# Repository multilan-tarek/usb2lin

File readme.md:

## USB2LIN

This is a 4-channel interface for LIN buses.\
It is using 4 NXP TJA1021 and a MaxLinear XR21V1414IM USB to UART bridge. 

Tested with BMW I/K-Bus, but it should work with any LIN bus.

---

### Gerber Files 
The gerber file is ready for ordering at JLCPCB.

### Parts
The schematic contains LCSC part numbers which can be exported to a BOM.

### Udev rules
This repository contains a udev rules file that maps the UART ports to ```/dev/lin/a@,b@,c@,d@```, matching the boards silkscreen.

---

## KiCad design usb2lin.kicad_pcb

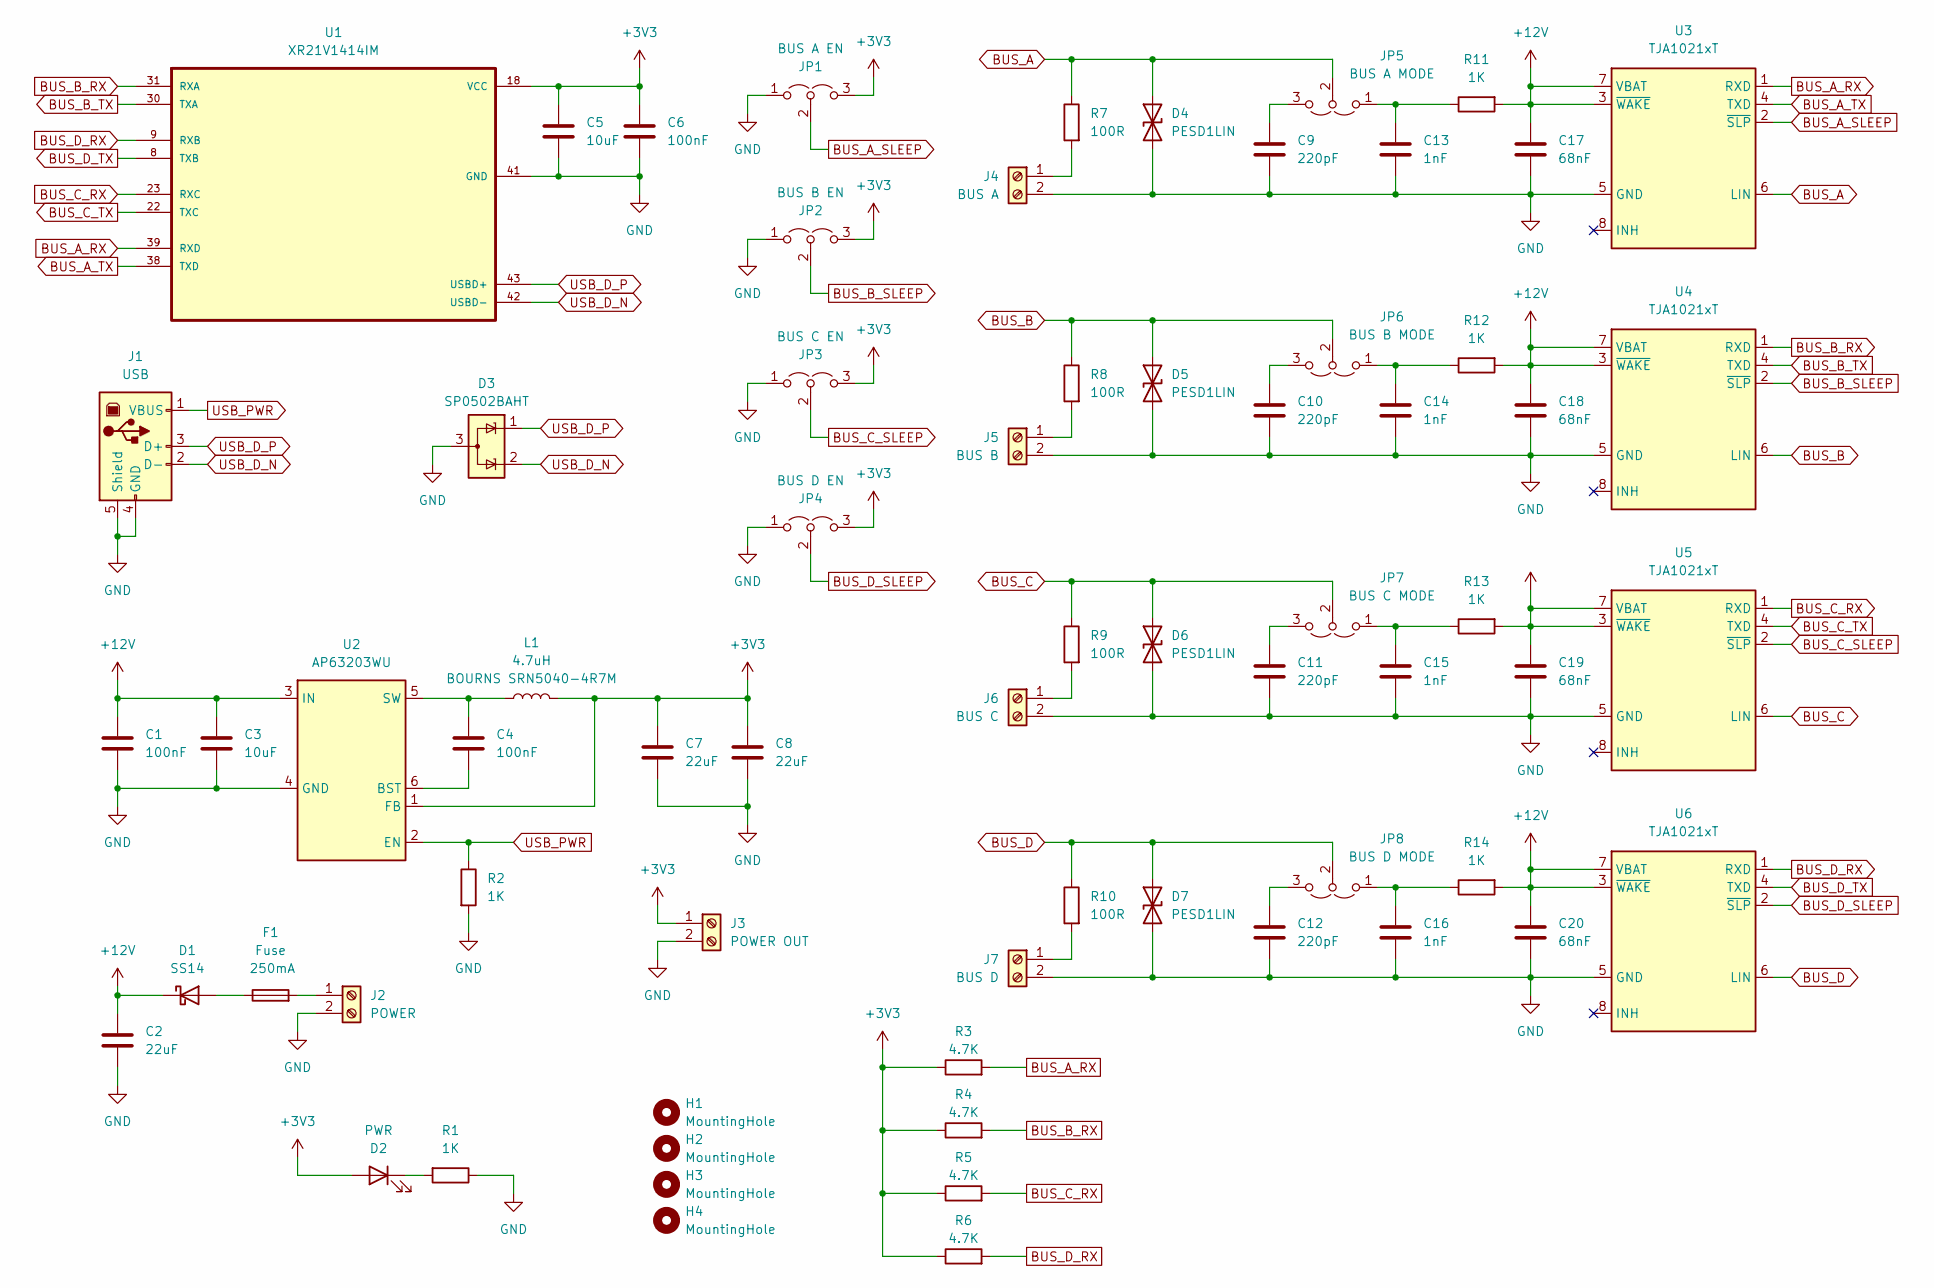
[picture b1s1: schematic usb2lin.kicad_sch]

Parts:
C1, C4, C6: 100nF; C_0805_2012Metric; LCSC C1711
C2, C7, C8: 22uF; C_0805_2012Metric; LCSC C602037
C3, C5: 10uF; C_0805_2012Metric; LCSC C15850
C9, C10, C11, C12: 220pF; C_0805_2012Metric; LCSC C472838
C13, C14, C15, C16: 1nF; C_0805_2012Metric; LCSC C46653
C17, C18, C19, C20: 68nF; C_0805_2012Metric; LCSC C472830
D1: SS14; D_SMA; LCSC C83852
D2: PWR; LED_0805_2012Metric; LCSC C94868
D3: SP0502BAHT; SOT-23; LCSC C207261
D4, D5, D6, D7: PESD1LIN; D_SOD-323; LCSC C58901
F1: Fuse; Fuse_1206_3216Metric_Pad1.42x1.75mm_HandSolder; LCSC C83557
H1, H2, H3, H4: MountingHole; MountingHole_3.2mm_M3
J1: USB; USB_B_TE_5787834_Vertical; LCSC C592900
J2: POWER; TerminalBlock_TE_282834-2_1x02_P2.54mm_Horizontal; LCSC C592983
J3: POWER OUT; TerminalBlock_TE_282834-2_1x02_P2.54mm_Horizontal; LCSC C592983
J4: BUS A; TerminalBlock_TE_282834-2_1x02_P2.54mm_Horizontal; LCSC C592983
J5: BUS B; TerminalBlock_TE_282834-2_1x02_P2.54mm_Horizontal; LCSC C592983
J6: BUS C; TerminalBlock_TE_282834-2_1x02_P2.54mm_Horizontal; LCSC C592983
J7: BUS D; TerminalBlock_TE_282834-2_1x02_P2.54mm_Horizontal; LCSC C592983
JP1: BUS A EN; PinHeader_1x03_P2.54mm_Vertical; LCSC C2937625
JP2: BUS B EN; PinHeader_1x03_P2.54mm_Vertical; LCSC C2937625
JP3: BUS C EN; PinHeader_1x03_P2.54mm_Vertical; LCSC C2937625
JP4: BUS D EN; PinHeader_1x03_P2.54mm_Vertical; LCSC C2937625
JP5: BUS A MODE; PinHeader_1x03_P2.54mm_Vertical; LCSC C2937625
JP6: BUS B MODE; PinHeader_1x03_P2.54mm_Vertical; LCSC C2937625
JP7: BUS C MODE; PinHeader_1x03_P2.54mm_Vertical; LCSC C2937625
JP8: BUS D MODE; PinHeader_1x03_P2.54mm_Vertical; LCSC C2937625
L1: 4.7uH; L_APV_ANR5040; LCSC C2041710
R1, R2, R11, R12, R13, R14: 1K; R_0805_2012Metric; LCSC C441981
R3, R4, R5, R6: 4.7K; R_0805_2012Metric; LCSC C336873
R7, R8, R9, R10: 100R; R_0805_2012Metric; LCSC C193990
U1: XR21V1414IM; TQFP-48_7x7mm_P0.5mm; MPN XR21V1414IM-0B-EB; LCSC C141719
U2: AP63203WU; TSOT-23-6; LCSC C780769
U3, U4, U5, U6: TJA1021xT; SOIC-8_3.9x4.9mm_P1.27mm; LCSC C182937

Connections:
+3V3: C5.1, C6.1, C7.1, C8.1, D2.2 (A), J3.1, JP1.3 (B), JP2.3 (B), JP3.3 (B), JP4.3 (B), L1.2, R3.1, R4.1, R5.1, R6.1, U1.5 (VCC), U1.18 (VCC), U1.33 (VCC), U1.44 (VCC), U1.45 (VCC), U2.1 (FB)
+12V: C1.1, C2.1, C3.1, C17.1, C18.1, C19.1, C20.1, D1.1 (K), R11.2, R12.2, R13.2, R14.2, U2.3 (IN), U3.3 (~WAKE), U3.7 (VBAT), U4.3 (~WAKE), U4.7 (VBAT), U5.3 (~WAKE), U5.7 (VBAT), U6.3 (~WAKE), U6.7 (VBAT)
BUS_A: D4.1 (A1), JP5.2 (C), R7.1, U3.6 (LIN)
BUS_A_RX: R3.2, U1.39 (RXD), U3.1 (RXD)
BUS_A_SLEEP: JP1.2 (C), U3.2 (~SLP)
BUS_A_TX: U1.38 (TXD), U3.4 (TXD)
BUS_B: D5.1 (A1), JP6.2 (C), R8.1, U4.6 (LIN)
BUS_B_RX: R4.2, U1.31 (RXA), U4.1 (RXD)
BUS_B_SLEEP: JP2.2 (C), U4.2 (~SLP)
BUS_B_TX: U1.30 (TXA), U4.4 (TXD)
BUS_C: D6.1 (A1), JP7.2 (C), R9.1, U5.6 (LIN)
BUS_C_RX: R5.2, U1.23 (RXC), U5.1 (RXD)
BUS_C_SLEEP: JP3.2 (C), U5.2 (~SLP)
BUS_C_TX: U1.22 (TXC), U5.4 (TXD)
BUS_D: D7.1 (A1), JP8.2 (C), R10.1, U6.6 (LIN)
BUS_D_RX: R6.2, U1.9 (RXB), U6.1 (RXD)
BUS_D_SLEEP: JP4.2 (C), U6.2 (~SLP)
BUS_D_TX: U1.8 (TXB), U6.4 (TXD)
GND: C1.2, C2.2, C3.2, C5.2, C6.2, C7.2, C8.2, C9.2, C10.2, C11.2, C12.2, C13.2, C14.2, C15.2, C16.2, C17.2, C18.2, C19.2, C20.2, D3.3 (A), D4.2 (A2), D5.2 (A2), D6.2 (A2), D7.2 (A2), J1.4 (GND), J1.5 (Shield), J2.2, J3.2, J4.2, J5.2, J6.2, J7.2, JP1.1 (A), JP2.1 (A), JP3.1 (A), JP4.1 (A), R1.1, R2.2, U1.1 (GND), U1.4 (GND), U1.19 (GND), U1.32 (GND), U1.40 (GND), U1.41 (GND), U2.4 (GND), U3.5 (GND), U4.5 (GND), U5.5 (GND), U6.5 (GND)
unnamed: D1.2 (A), F1.1
unnamed: D2.1 (K), R1.2
unnamed: F1.2, J2.1
unnamed: J4.1, R7.2
unnamed: J5.1, R8.2
unnamed: J6.1, R9.2
unnamed: J7.1, R10.2
unnamed: C13.1, JP5.1 (A), R11.1
unnamed: C9.1, JP5.3 (B)
unnamed: C14.1, JP6.1 (A), R12.1
unnamed: C10.1, JP6.3 (B)
unnamed: C15.1, JP7.1 (A), R13.1
unnamed: C11.1, JP7.3 (B)
unnamed: C16.1, JP8.1 (A), R14.1
unnamed: C12.1, JP8.3 (B)
unnamed: C4.2, U2.6 (BST)
unnamed: C4.1, L1.1, U2.5 (SW)
USB_D_N: D3.2 (K), J1.2 (D-), U1.42 (USBD-)
USB_D_P: D3.1 (K), J1.3 (D+), U1.43 (USBD+)
USB_PWR: J1.1 (VBUS), R2.1, U2.2 (EN)

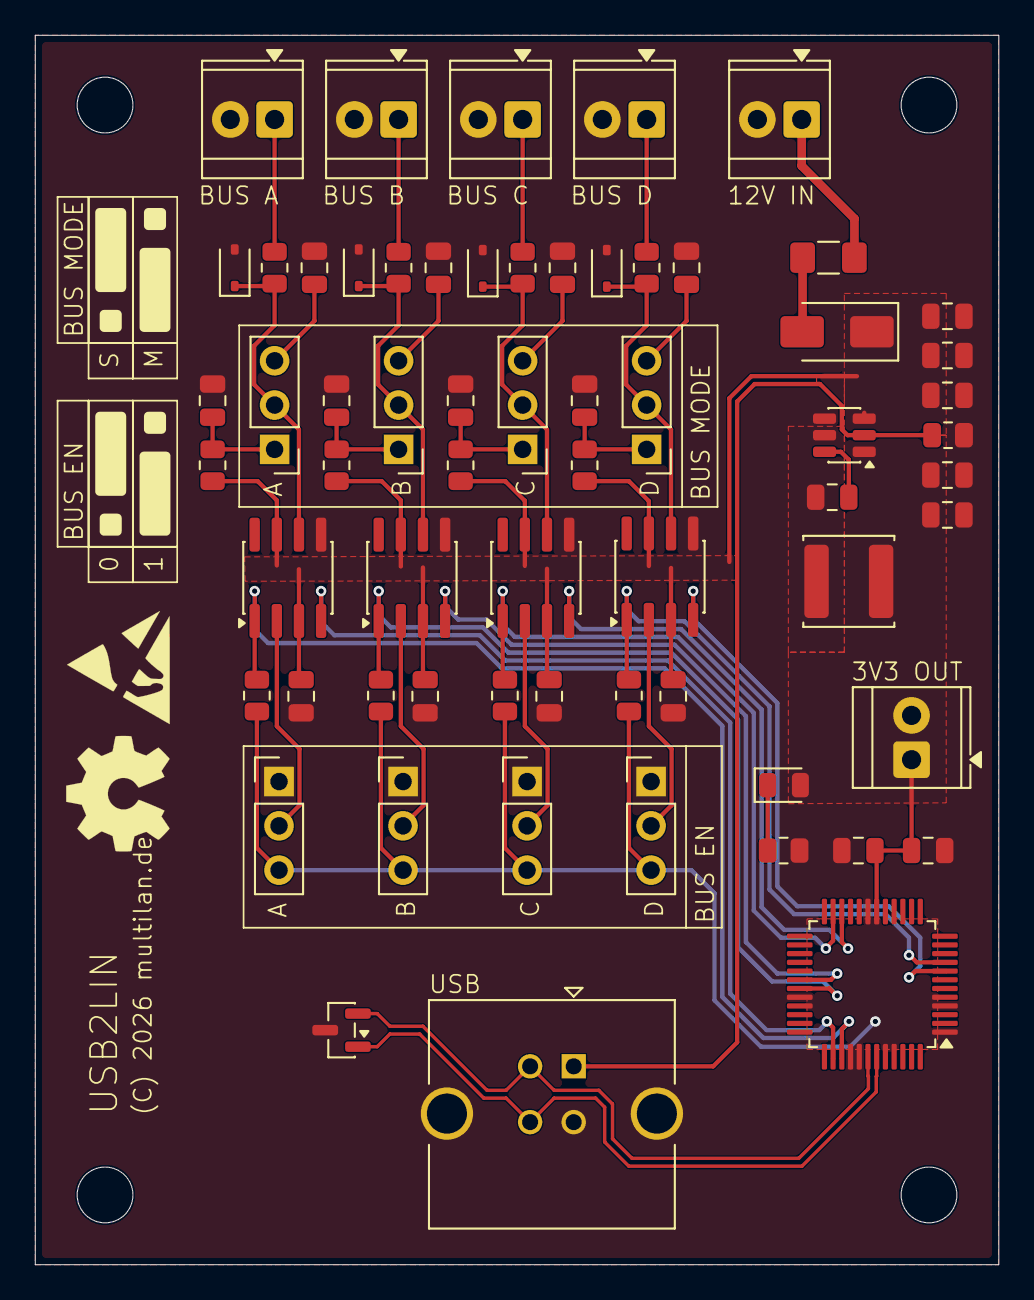
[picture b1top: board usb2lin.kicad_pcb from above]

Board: 2 copper layers, 55.2 x 70.5 mm, 68 parts (0 on the bottom side), 39 nets.

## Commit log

2026-04-19 Added images
2026-04-19 Add license
2026-04-19 Compressed images
2026-04-19 udev rules now map to /dev/lin/*

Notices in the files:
usb2lin.kicad_pcb:
(C) 2026 multilan.de
